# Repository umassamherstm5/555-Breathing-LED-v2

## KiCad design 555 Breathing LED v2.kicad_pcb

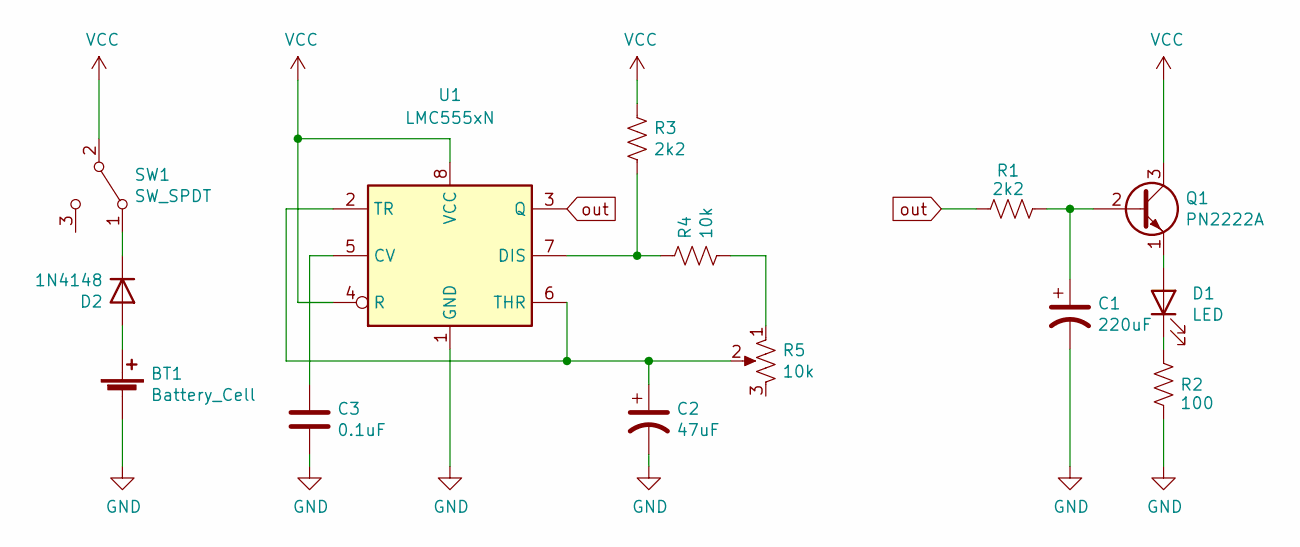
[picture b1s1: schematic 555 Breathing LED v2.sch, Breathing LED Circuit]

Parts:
BT1: Battery_Cell; BatteryHolder_MPD_BA9VPC_1xPP3noholes
C1: 220uF; CP_Radial_D6.3mm_P2.50mm
C2: 47uF; CP_Radial_D6.3mm_P2.50mm
C3: 0.1uF; C_Disc_D5.0mm_W2.5mm_P2.50mm
D1: LED; LED_D10.0mm
D2: 1N4148; D_DO-35_SOD27_P7.62mm_Horizontal
Q1: PN2222A; TO-92L_Wide
R1, R3: 2k2; R_Axial_DIN0309_L9.0mm_D3.2mm_P12.70mm_Horizontal
R2: 100; R_Axial_DIN0309_L9.0mm_D3.2mm_P12.70mm_Horizontal
R4: 10k; R_Axial_DIN0309_L9.0mm_D3.2mm_P12.70mm_Horizontal
R5: 10k; Potentiometer_Bourns_PTA2043_Single_Slide
SW1: SW_SPDT; MHS12204_SPDT
U1: LMC555xN; DIP-8_W7.62mm

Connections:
GND: BT1.2 (-), C1.2, C2.2, C3.2, R2.2, U1.1 (GND)
unnamed: BT1.1 (+), D2.2 (A)
unnamed: C1.1, Q1.2 (B), R1.2
unnamed: C2.1, R5.2, U1.2 (TR), U1.6 (THR)
unnamed: C3.1, U1.5 (CV)
unnamed: D1.1 (K), R2.1
unnamed: D1.2 (A), Q1.1 (E)
unnamed: D2.1 (K), SW1.1 (A)
unnamed: R3.2, R4.1, U1.7 (DIS)
unnamed: R4.2, R5.1
VCC: Q1.3 (C), R3.1, SW1.2 (B), U1.4 (R), U1.8 (VCC)
out: R1.1, U1.3 (Q)

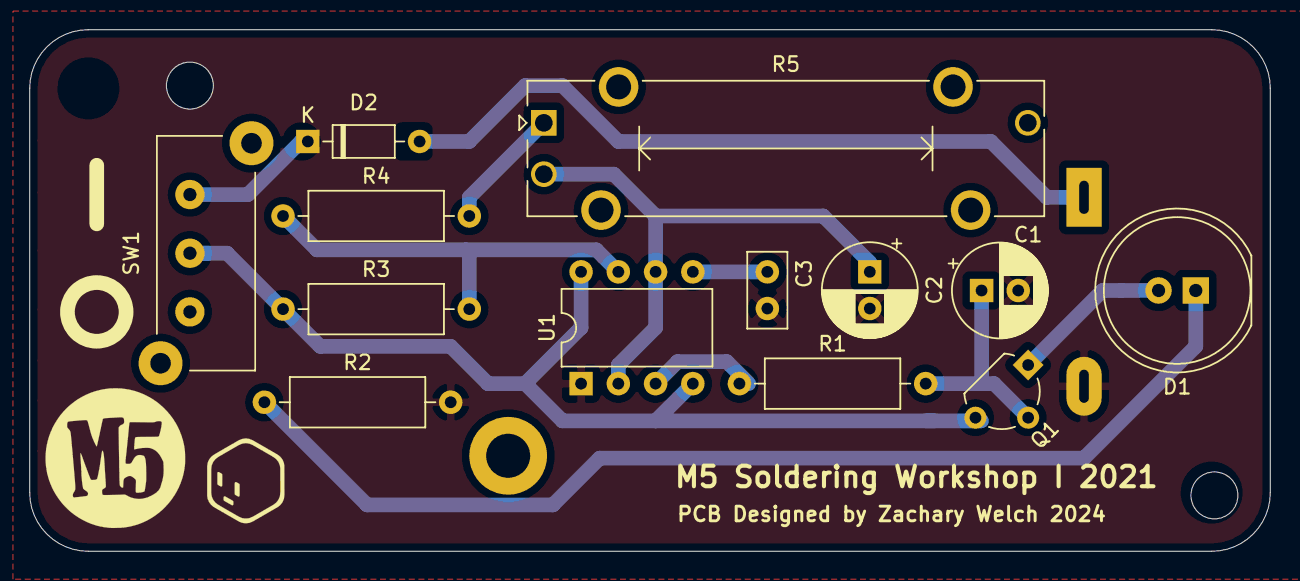
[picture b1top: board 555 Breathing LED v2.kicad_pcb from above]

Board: 2 copper layers, 84.6 x 35.6 mm, 14 parts (1 on the bottom side), 12 nets.

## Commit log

2021-09-11 First schematic
2021-09-13 Updated Schematic
2021-09-16 updated footprint of C3
2021-09-16 created pcb
2021-09-16 moved pcb components
2021-09-18 developed pcb
2021-09-21 Update fp-info-cache
2021-09-21 Finished PCB
2021-09-21 Exported
2021-10-29 Updated, epic fortnite
2021-10-31 File Export
2021-10-31 Updated export
2021-10-31 Fixed resistor placement error
2021-11-19 fixed diode
